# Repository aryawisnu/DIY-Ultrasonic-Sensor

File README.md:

# DIY-Ultrasonic-Sensor
Tugas Besar Kuliah Semester 3  
______________________________________________________________________________________
Repo ini berisi tentang proyek DIY Ultrasonic sensor  
Pada perkuliahan semester 3 ini kita diberi tugas untuk membuat suatu module sensor  
Kelompok ini mendapat bagian sensor yang berhubungan dengan suara  
Maka dari itu pada tugas ini kita memilih untuk membuat module sensor ultrasonic  
______________________________________________________________________________________
Pada module sensor ultrasonic ini kita menggunakan komponen-komponen sebagai berikut :  
=> Op-Amp LM324  
=> Max232  
=> Atmega328p  
=> Attiny85  
Semua komponen yang digunakan pada module sensor ini menggunakan package SMD  
## Berikut skematik rangkaian dari module sensor ultrasonic ini :  
  
## Berikut fungsi dari tiap-tiap blok diatas :  
> Transducer

Berisi transducer berupa receiver dan transmitter ultrasonic  
> Transducer TX Driver

Berisi ic MAX232 yang digunakan sebagai voltage multiplier. Block ini akan mengkonversi tegangan sinyal masukan dari mikrokontroller atmega328p yang hanya sebesar 5V menjadi tegangan sebesar 7-10V yang selanjutnya diteruskan kepada ultrasonic transmitter. Proses step up tegangan ini digunakan untuk menambah jangkauan dari ultrasonic transmitter  
> Amplifier RX Transducer

Block ini digunakan untuk menguatkan sinyal yang diterima oleh ultrasonic receiver agar bisa terbaca oleh ADC atmega328p. Block ini memanfaatkan ic op-amp LM324 yang merupakan sebuah ic yang berisi 4 op-amp didalamnya. Keluaran dari block ini terhubung dengan pin ADC atmega328p yang selanjutnya akan diolah  
> Kontroller Ultrasonic

Block ini digunakan untuk mengontrol proses dari sensor ultrasonic. Block ini mengirimkan perintah ke Transducer TX Driver dan menerima masukan sinyal dari Amplifier RX Transducer. Pada block ini berisi ic atmega328p, proses control ultrasonic dapat dikontrol melalui pin ECHO dan TRIG yang dimana pin ini akan terkoneksi dengan ic attiny85  
> Temp Sensor

Block ini berisi sensor temperature berupa NTC 10k yang digunakan untuk membaca temperature dari modul sensor yan dibuat. Keluaran block ini terhubung dengan pin ADC attiny85  
> Kontroller UART dan Temp Sensor

Pada block ini berisi ic attiny85. Block ini digunakan untuk mengontrol pin ECHO dan TRIG dari controller ultrasonic lalu mengubahnya menjadi besaran panjang. Block ini juga digunakan untuk membaca masukan dari temp sensor lalu mengkonversinya menjadi besaran temperature. Selanjutnya besaran panjang dan temperature akan dikeluarkan melalui pin serial dari attiny85 yang selanjutnya data serial panjang dan temperature ini dapat dibaca melalui komunikasi serial UART dan diolah oleh controller selanjutnya. Kontroller selanjutnya dapat berupa ESP8266 yang dapat mengirimkan data panjang dan temperature melalui IoT  
> Konektor
  
Block ini berisi pinheader yang digunakan sebagai konektor pada modul sensor ini  
## Berikut merupakan gambar render dari PCB sensor ultrasonic ini :  
> Layer Atas

> Layer Bawah

## Berikut merupakan gambar PCB yang sudah tercetak :  
> Tampak Atas

> Tampak Bawah

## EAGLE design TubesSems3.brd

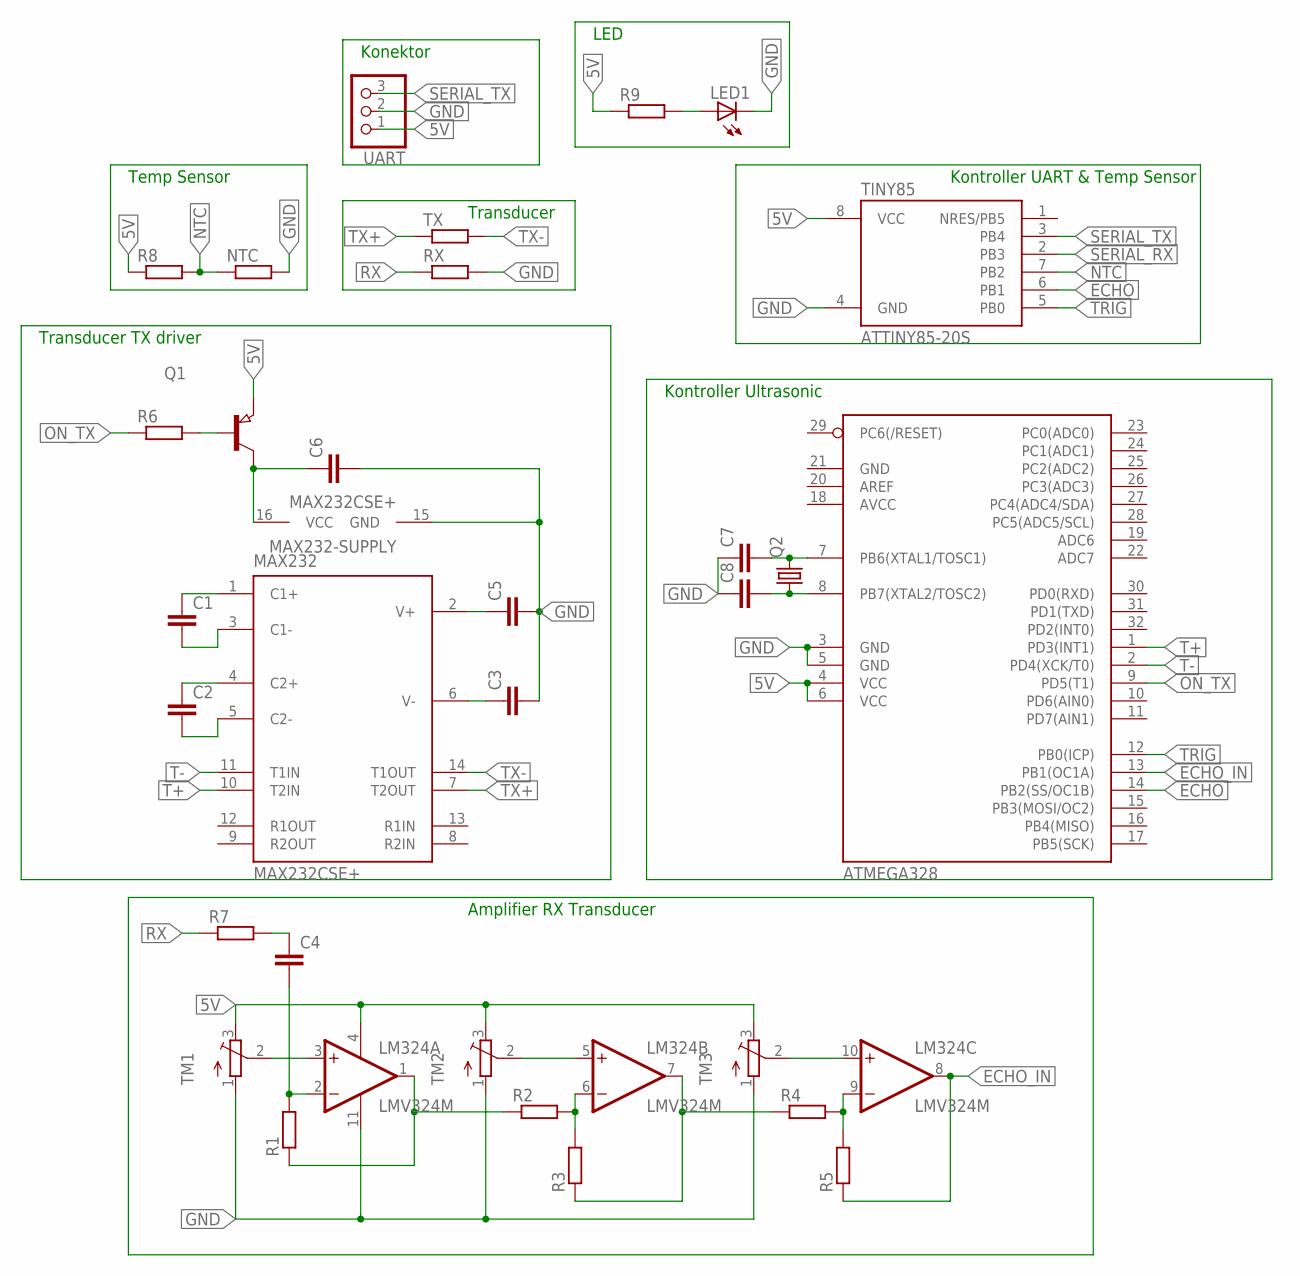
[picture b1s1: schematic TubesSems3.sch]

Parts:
ATMEGA328: MEGA8-AI; TQFP32-08
C1, C2, C3, C4, C5, C6: C-EUC0603; C0603
C7, C8: C-EUC0805; C0805
LED1: LEDCHIPLED_1206; CHIPLED_1206
LM324: LMV324M; SO14
MAX232: MAX232CSE+; SO-16
NTC: R-EU_R0805; R0805
Q1: PNP-TRANSISTOR_SOT23; SOT23
Q2: CRYSTALSM49; SM49
R1, R2, R3, R4, R5, R6, R7: R-EU_R1206; R1206
R8: R-EU_R0805; R0805
R9: R-EU_M1206; M1206
RX: R-EU_0207/11; 0207/11
TINY85: ATTINY85-20S; SOIC8_EIAJ_208MIL
TM1, TM2, TM3: TRIMPOTTC33X; TC33X
TX: R-EU_0207/11; 0207/11
UART: PINHD-1X3; 1X03

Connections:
5V: ATMEGA328.4 (VCC), ATMEGA328.6 (VCC), LM324.4 (V+), Q1.2 (E), R8.1, R9.1, TINY85.8 (VCC), TM1.3 (E), TM2.3 (E), TM3.3 (E), UART.1
AVCC: ATMEGA328.18 (AVCC)
ECHO: ATMEGA328.14 (PB2(SS/OC1B)), TINY85.6 (PB1)
ECHO_IN: ATMEGA328.13 (PB1(OC1A)), LM324.8 (OUT), R5.1
GND: ATMEGA328.3 (GND), ATMEGA328.5 (GND), ATMEGA328.21 (GND), C3.2, C5.2, C6.2, C7.1, C8.1, LED1.C, LM324.11 (V-), MAX232.15 (GND), NTC.2, RX.2, TINY85.4 (GND), TM1.1 (A), TM2.1 (A), TM3.1 (A), UART.2
unnamed: C1.1, MAX232.1 (C1+)
unnamed: C1.2, MAX232.3 (C1-)
unnamed: C2.1, MAX232.4 (C2+)
unnamed: C2.2, MAX232.5 (C2-)
unnamed: C3.1, MAX232.6 (V-)
unnamed: C5.1, MAX232.2 (V+)
unnamed: ATMEGA328.7 (PB6(XTAL1/TOSC1)), C7.2, Q2.2
unnamed: C6.1, MAX232.16 (VCC), Q1.3 (C)
unnamed: LM324.3 (+IN), TM1.2 (S)
unnamed: C4.2, LM324.2 (-IN), R1.2
unnamed: LM324.1 (OUT), R1.1, R2.1
unnamed: LM324.5 (+IN), TM2.2 (S)
unnamed: LM324.6 (-IN), R2.2, R3.2
unnamed: Q1.1 (B), R6.2
unnamed: LM324.7 (OUT), R3.1, R4.1
unnamed: LM324.10 (+IN), TM3.2 (S)
unnamed: LM324.9 (-IN), R4.2, R5.2
unnamed: ATMEGA328.8 (PB7(XTAL2/TOSC2)), C8.2, Q2.1
unnamed: C4.1, R7.2
unnamed: LED1.A, R9.2
NTC: NTC.1, R8.2, TINY85.7 (PB2)
ON_TX: ATMEGA328.9 (PD5(T1)), R6.1
RX: R7.1, RX.1
SERIAL_RX: TINY85.2 (PB3)
SERIAL_TX: TINY85.3 (PB4), UART.3
T+: ATMEGA328.1 (PD3(INT1)), MAX232.10 (T2IN)
T-: ATMEGA328.2 (PD4(XCK/T0)), MAX232.11 (T1IN)
TRIG: ATMEGA328.12 (PB0(ICP)), TINY85.5 (PB0)
TX+: MAX232.7 (T2OUT), TX.1
TX-: MAX232.14 (T1OUT), TX.2

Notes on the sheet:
Transducer
Temp Sensor
Amplifier RX Transducer
Transducer TX driver
Konektor
Kontroller UART & Temp Sensor
Kontroller Ultrasonic
LED

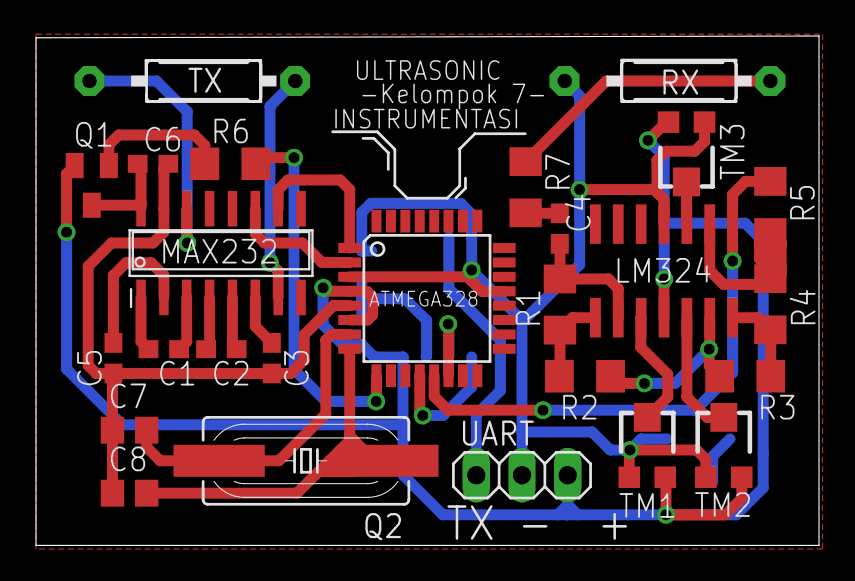
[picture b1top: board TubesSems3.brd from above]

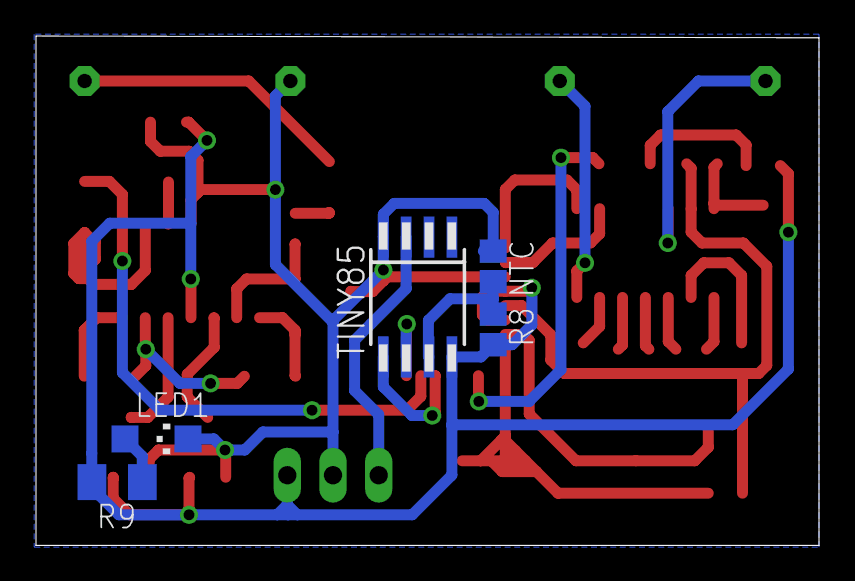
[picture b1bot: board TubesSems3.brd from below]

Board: 2 copper layers, 43.5 x 28.3 mm, 31 parts (5 on the bottom side), 33 nets.

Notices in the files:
parts and their libraries:
maxim-volks73: Creative Commons Attribution-ShareAlike 3.0 Unported (CC BY-SA 3.0), http://creativecommons.org/licenses/by-sa/3.0/.
